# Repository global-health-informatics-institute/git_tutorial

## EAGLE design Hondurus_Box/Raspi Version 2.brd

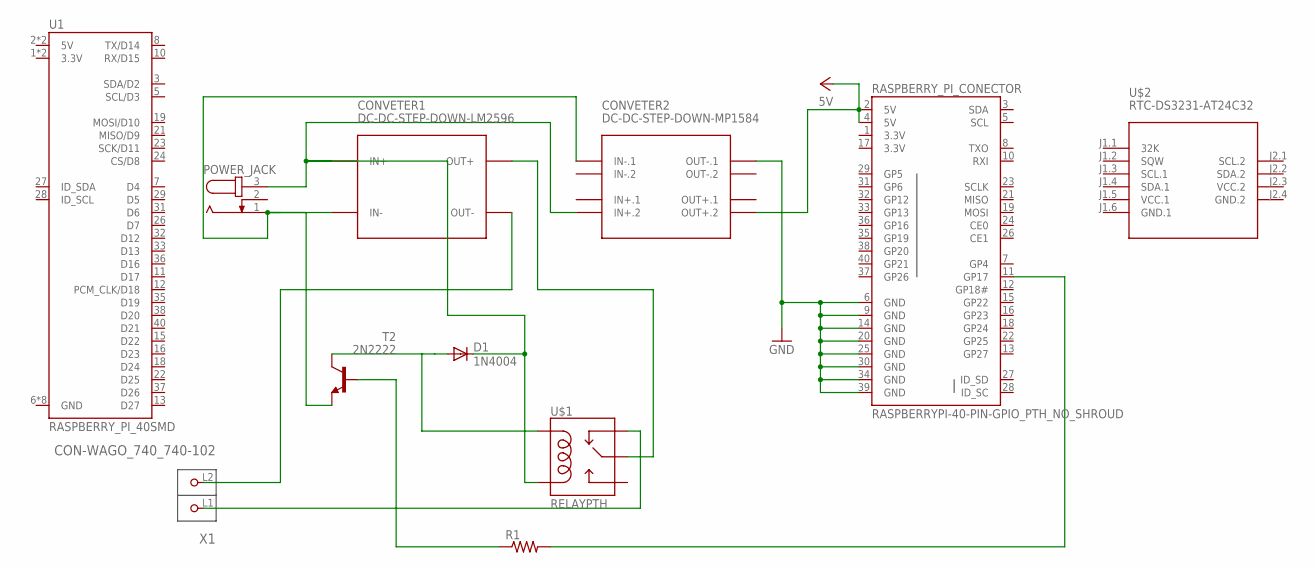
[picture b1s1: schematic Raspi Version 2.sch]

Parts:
CONVETER1: DC-DC-STEP-DOWN-LM2596
CONVETER2: DC-DC-STEP-DOWN-MP1584
D1: 1N4004; DO41-10
POWER_JACK: JACK-PLUG0; SPC4077
R1: R-US_0207/10; 0207/10
RASPBERRY_PI_CONECTOR: RASPBERRYPI-40-PIN-GPIO_PTH_NO_SHROUD; 2X20
T2: 2N2222; TO92-EBC-OVAL
U1: RASPBERRY_PI_40SMD; RASPBERRY_PI_SHIELD_HOLES
U$1: RELAYPTH; SRD-05VDC-SL-C
U$2: RTC-DS3231-AT24C32
X1: CON-WAGO_740_740-102; CON-WAGO_740_P-740-102

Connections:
3.3V: RASPBERRY_PI_CONECTOR.1 (3.3V), RASPBERRY_PI_CONECTOR.17 (3.3V)
GND: CONVETER2.OUT-.1, RASPBERRY_PI_CONECTOR.6 (GND), RASPBERRY_PI_CONECTOR.9 (GND), RASPBERRY_PI_CONECTOR.14 (GND), RASPBERRY_PI_CONECTOR.20 (GND), RASPBERRY_PI_CONECTOR.25 (GND), RASPBERRY_PI_CONECTOR.30 (GND), RASPBERRY_PI_CONECTOR.34 (GND), RASPBERRY_PI_CONECTOR.39 (GND)
GND.1: U$2.J1.6 (GND.1)
GND.2: U$2.J2.4 (GND.2)
unnamed: CONVETER1.IN+, CONVETER2.IN+.2, D1.C, POWER_JACK.3, U$1.COIL0
unnamed: CONVETER1.OUT-, X1.L2 (P2)
unnamed: CONVETER1.IN-, CONVETER2.IN-.1, POWER_JACK.1, T2.E
unnamed: R1.2, RASPBERRY_PI_CONECTOR.11 (GP17)
unnamed: D1.A, T2.C, U$1.COIL1
unnamed: R1.1, T2.B
unnamed: U$1.SWCLOSED (SWCLOSE), X1.L1 (P1)
unnamed: CONVETER1.OUT+, U$1.SWCOMMON
VCC: CONVETER2.OUT+.2, RASPBERRY_PI_CONECTOR.2 (5V), RASPBERRY_PI_CONECTOR.4 (5V)
VCC.1: U$2.J1.5 (VCC.1)
VCC.2: U$2.J2.3 (VCC.2)

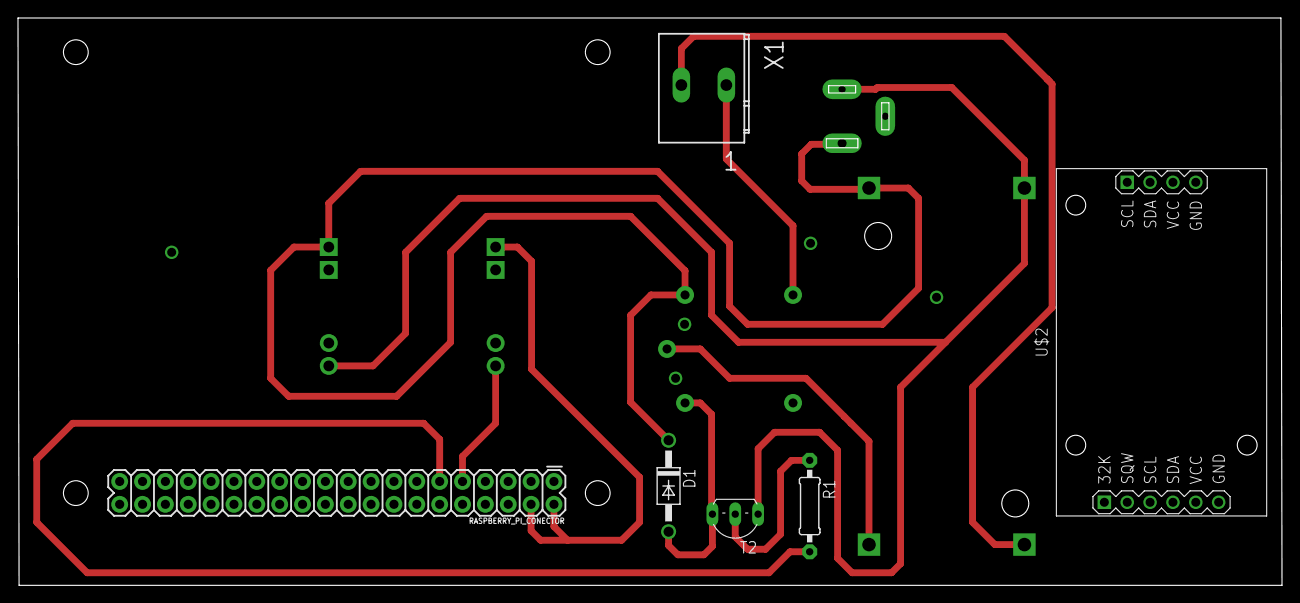
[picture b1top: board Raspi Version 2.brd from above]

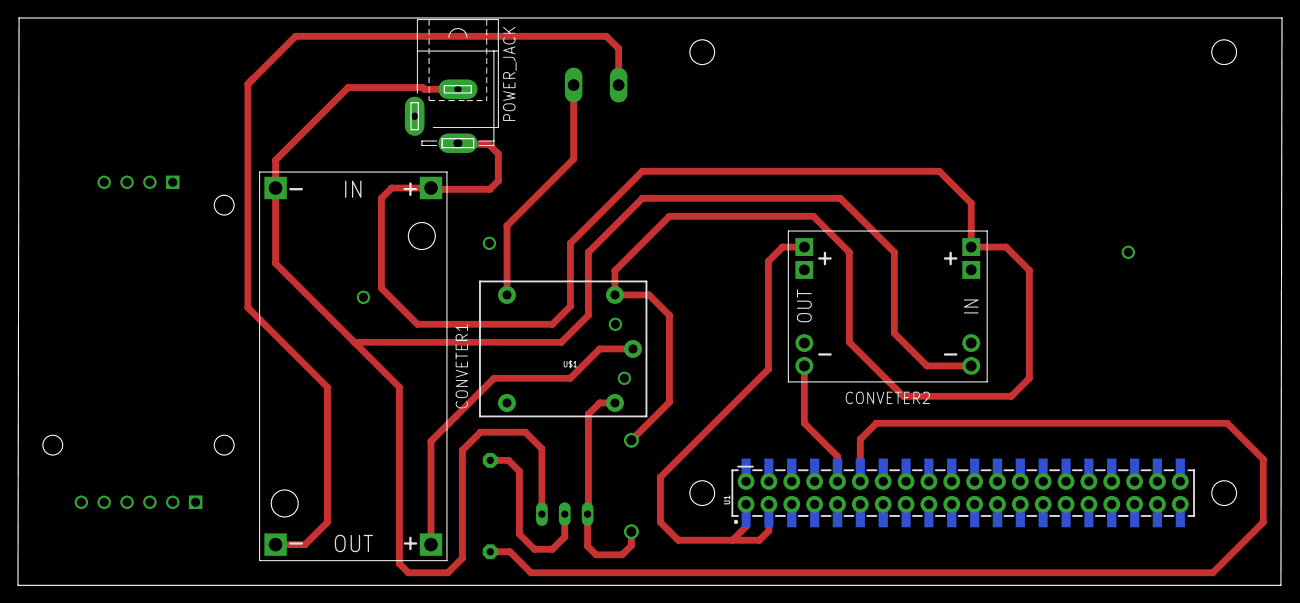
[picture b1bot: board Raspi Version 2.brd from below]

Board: 2 copper layers, 140.5 x 63.0 mm, 11 parts (5 on the bottom side), 11 nets.

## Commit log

2019-10-07 second change
2019-10-08 Schematic and board files for the Hondurus Box circuit baord
2019-10-08 C++ Project
2019-10-08 the first file that am putting
2019-10-08 Electronic BP system
2019-10-08 plastic been cut
2019-10-09 Node red is the best!!
2019-10-23 RFID Log in System with a python code

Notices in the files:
parts and their libraries:
SparkFun-Connectors: Licensing: Creative Commons ShareAlike 4.0 International - https://creativecommons.org/licenses/by-sa/4.0
GHIdiy-modules: Released under the Creative Commons Attribution 4.0 International License: http://creativecommons.org/licenses/by/4.0
